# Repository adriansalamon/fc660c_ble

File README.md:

# FC660C BLE Alt Controller

Design files for a custom programmable keyboard controller for Leopold FC660C keyboard with QMK and Bluetooth support. This project is heavily inspired by Hasu's FC660C Alt Controller (https://geekhack.org/index.php?topic=90317.0).

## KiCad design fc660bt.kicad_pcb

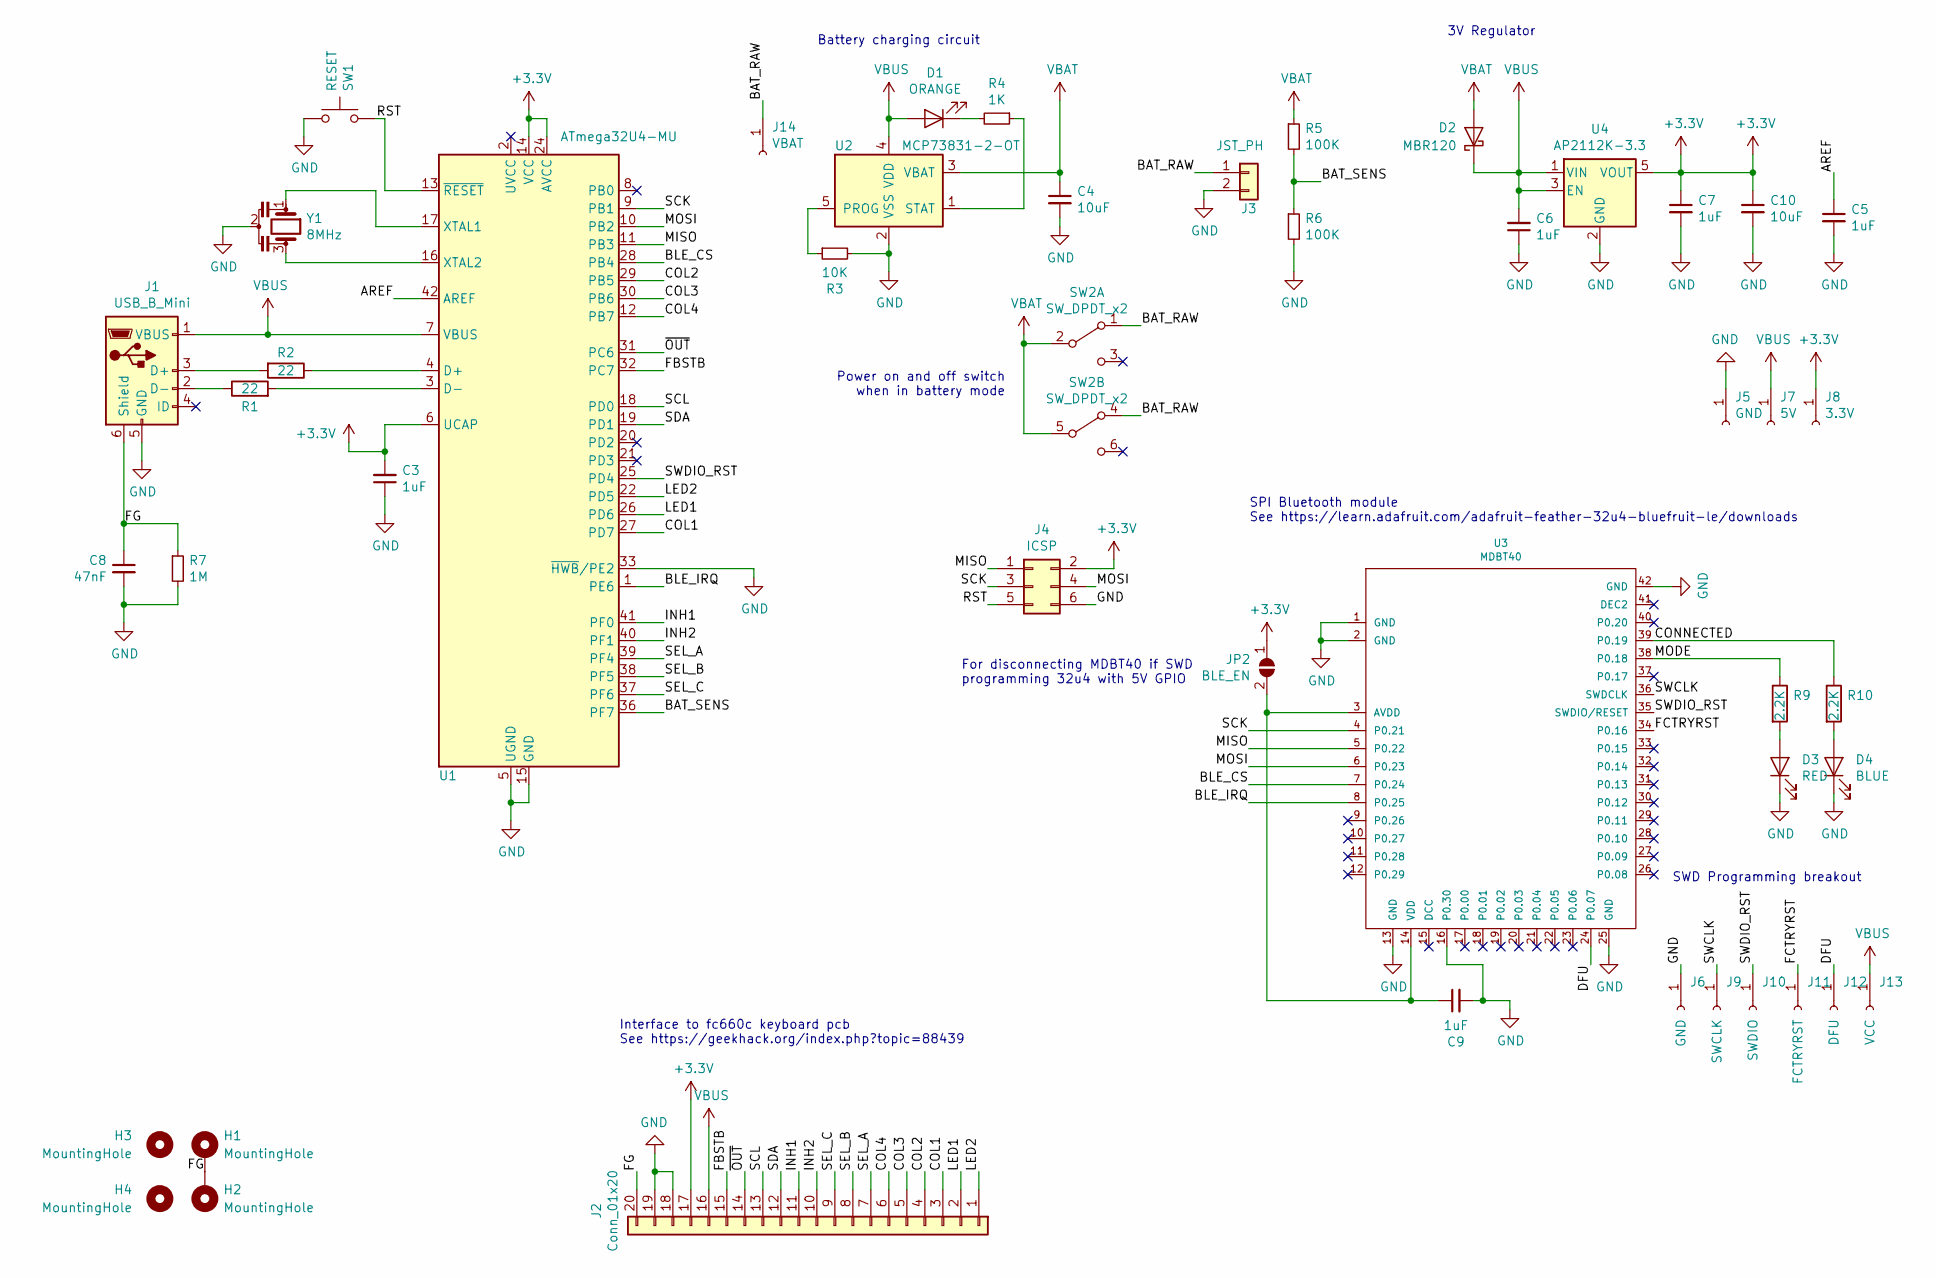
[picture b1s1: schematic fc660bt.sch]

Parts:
C3, C5, C6, C7, C9: 1uF; C_0805_2012Metric
C4, C10: 10uF; C_0805_2012Metric
C8: 47nF; C_0805_2012Metric
D1: ORANGE; LED_0805_2012Metric
D2: MBR120; D_SOD-123
D3: RED; LED_0805_2012Metric
D4: BLUE; LED_0805_2012Metric
H1, H2: MountingHole; MountingHole_2.7mm_Pad
H3, H4: MountingHole; Hole_Pins
J1: USB_B_Mini; USB_miniB_hirose_5S8
J2: Conn_01x20; HRS_DF14_20P
J3: JST_PH; JST_PH_S2B-PH-K_1x02_P2.00mm_Horizontal
J4: ICSP; AVR_ICSP_3x2
J5, J6: GND; PIN_1
J7: 5V; PIN_1
J8: 3.3V; PIN_1
J9: SWCLK; PIN_1
J10: SWDIO; PIN_1
J11: FCTRYRST; PIN_1
J12: DFU; PIN_1
J13: VCC; PIN_1
J14: VBAT; PIN_1
JP2: BLE_EN; SOLDER_JUMPER_2
R1, R2: 22; R_0805_2012Metric
R3: 10K; R_0805_2012Metric
R4: 1K; R_0805_2012Metric
R5, R6: 100K; R_0805_2012Metric
R7: 1M; R_0805_2012Metric
R9, R10: 2.2K; R_0805_2012Metric
SW1: RESET; SW_PTS647
SW2: SW_DPDT_x2; JS202011CQN
U1: ATmega32U4-MU; TQFP-44_10x10mm
U2: MCP73831-2-OT; SOT23-5_HSOL
U3: MDBT40
U4: AP2112K-3.3; SOT23-5_HSOL
Y1: 8MHz; Resonator_SMD_muRata_CSTxExxV-3Pin_3.0x1.1mm_HandSoldering

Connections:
+3V3: C3.2, C7.1, C10.1, J2.17, J4.2, J8.1, JP2.1 (A), U1.6 (UCAP), U1.14 (VCC), U1.24 (AVCC), U1.34 (VCC), U1.44 (AVCC), U4.5 (VOUT)
/AREF: C5.1, U1.42 (AREF)
/BAT_RAW: J3.1, J14.1, SW2.1 (A), SW2.4 (A)
/BAT_SENS: R5.2, R6.1, U1.36 (PF7)
/BLE_CS: U1.28 (PB4), U3.7 (P0.24)
/BLE_IRQ: U1.1 (PE6), U3.8 (P0.25)
/COL1: J2.3, U1.27 (PD7)
/COL2: J2.4, U1.29 (PB5)
/COL3: J2.5, U1.30 (PB6)
/COL4: J2.6, U1.12 (PB7)
/CONNECTED: R10.1, U3.39 (P0.19)
/DFU: J12.1, U3.24 (P0.07)
/FBSTB: J2.15, U1.32 (PC7)
/FCTRYRST: J11.1, U3.34 (P0.16)
/FG: C8.1, H1.1, H2.1, J1.6 (Shield), J2.20, R7.1
/INH1: J2.11, U1.41 (PF0)
/INH2: J2.10, U1.40 (PF1)
/LED1: J2.2, U1.26 (PD6)
/LED2: J2.1, U1.22 (PD5)
/MISO: J4.1, U1.11 (PB3), U3.5 (P0.22)
/MODE: R9.1, U3.38 (P0.18)
/MOSI: J4.4, U1.10 (PB2), U3.6 (P0.23)
/RST: J4.5, SW1.1, U1.13 (~RESET)
/SCK: J4.3, U1.9 (PB1), U3.4 (P0.21)
/SCL: J2.13, U1.18 (PD0)
/SDA: J2.12, U1.19 (PD1)
/SEL_A: J2.7, U1.39 (PF4)
/SEL_B: J2.8, U1.38 (PF5)
/SEL_C: J2.9, U1.37 (PF6)
/SWCLK: J9.1, U3.36 (SWDCLK)
/SWDIO_RST: J10.1, U1.25 (PD4), U3.35 (SWDIO/RESET)
/~OUT: J2.14, U1.31 (PC6)
GND: C3.1, C4.2, C5.2, C6.1, C7.2, C8.2, C9.2, C10.2, D3.1 (K), D4.1 (K), J1.5 (GND), J2.18, J2.19, J3.2, J4.6, J5.1, J6.1, R3.2, R6.2, R7.2, SW1.2, U1.5 (UGND), U1.15 (GND), U1.23 (GND), U1.33 (~HWB~/PE2), U1.35 (GND), U1.43 (GND), U1.45 (GND), U2.2 (VSS), U3.1 (GND), U3.2 (GND), U3.13 (GND), U3.16 (P0.30), U3.25 (GND), U3.42 (GND), U4.2 (GND), Y1.2
unnamed: C9.1, JP2.2 (B), U3.3 (AVDD), U3.14 (VDD)
unnamed: D1.1 (K), R4.2
unnamed: D3.2 (A), R9.2
unnamed: D4.2 (A), R10.2
unnamed: J1.2 (D-), R1.1
unnamed: J1.3 (D+), R2.2
unnamed: R1.2, U1.3 (D-)
unnamed: R2.1, U1.4 (D+)
unnamed: R3.1, U2.5 (PROG)
unnamed: R4.1, U2.1 (STAT)
unnamed: U1.16 (XTAL2), Y1.3
unnamed: U1.17 (XTAL1), Y1.1
VBAT: C4.1, D2.2 (A), R5.1, SW2.2 (B), SW2.5 (B), U2.3 (VBAT)
VBUS: C6.2, D1.2 (A), D2.1 (K), J1.1 (VBUS), J2.16, J7.1, J13.1, U1.7 (VBUS), U2.4 (VDD), U4.1 (VIN), U4.3 (EN)

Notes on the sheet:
3V Regulator
Interface to fc660c keyboard pcb See https://geekhack.org/index.php?topic=88439
SPI Bluetooth module See https://learn.adafruit.com/adafruit-feather-32u4-bluefruit-le/downloads
For disconnecting MDBT40 if SWD programming 32u4 with 5V GPIO
SWD Programming breakout
Battery charging circuit
Power on and off switch when in battery mode

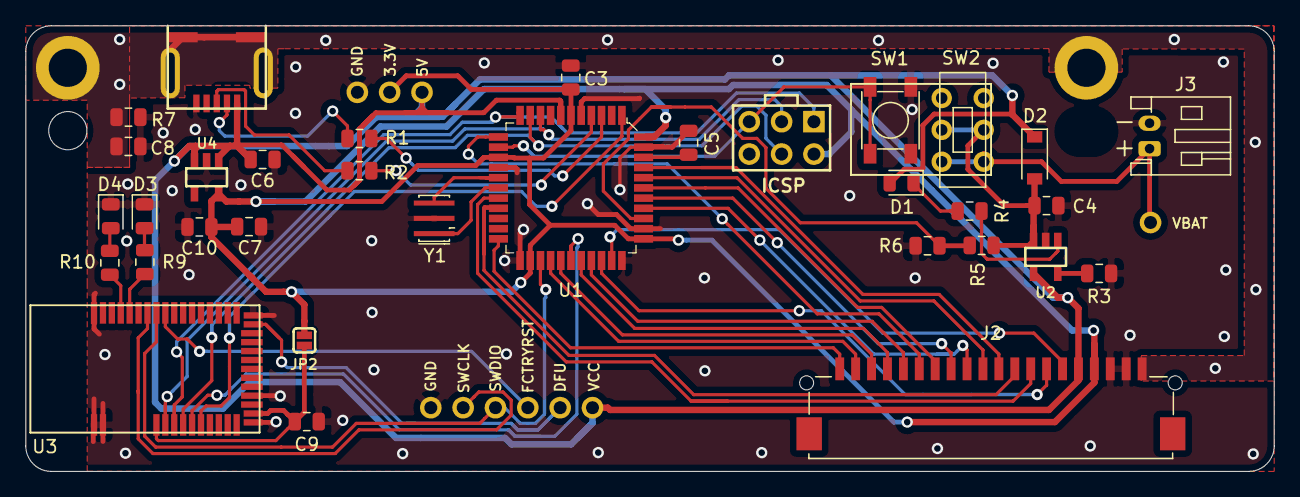
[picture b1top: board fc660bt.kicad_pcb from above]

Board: 2 copper layers, 98.0 x 35.0 mm, 47 parts (0 on the bottom side), 47 nets.

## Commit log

2020-01-10 Initial commit of project
2020-01-10 Added License
2020-01-10 Cleaned up and added comments to schematic
2020-01-11 Added switch to connect and disconnect battery
